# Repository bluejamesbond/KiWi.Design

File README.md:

Bolt.Design
===========

**Colors:**
*pink*: `#c13eca`
*purple*: `#50248b`
*dark blue*: `#171d25`

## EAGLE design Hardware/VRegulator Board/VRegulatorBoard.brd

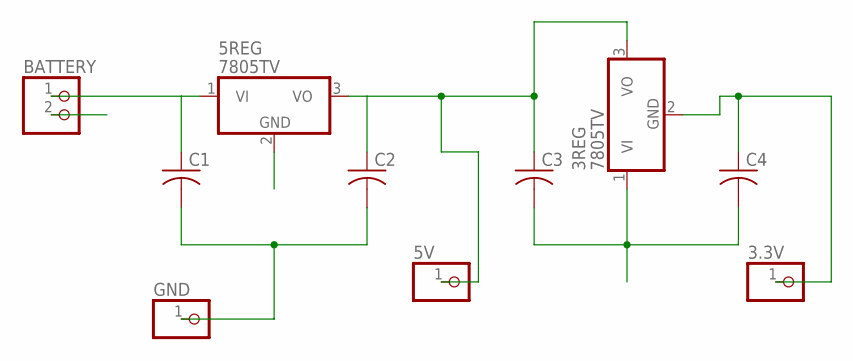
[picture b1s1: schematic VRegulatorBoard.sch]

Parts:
3.3V, 5V: PINHD-1X1; 1X01
3REG, 5REG: 7805TV; TO220V
BATTERY: PINHD-1X2; 1X02
C1, C2, C3, C4: C-US050-025X075; C050-025X075
GND: PINHD-1X1; 1X01

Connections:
5REGULATOR: 5REG.1 (VI), BATTERY.1, C1.1
GND: 3REG.1 (VI), 5REG.2 (GND), BATTERY.2, C1.2, C2.2, C3.2, C4.2, GND.1
unnamed: 3REG.3 (VO), 5REG.3 (VO), 5V.1, C2.1, C3.1
unnamed: 3.3V.1, 3REG.2 (GND), C4.1

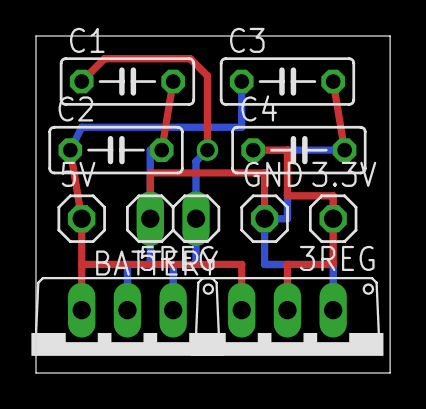
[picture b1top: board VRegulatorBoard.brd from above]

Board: 2 copper layers, 19.7 x 18.7 mm, 10 parts (0 on the bottom side), 4 nets.

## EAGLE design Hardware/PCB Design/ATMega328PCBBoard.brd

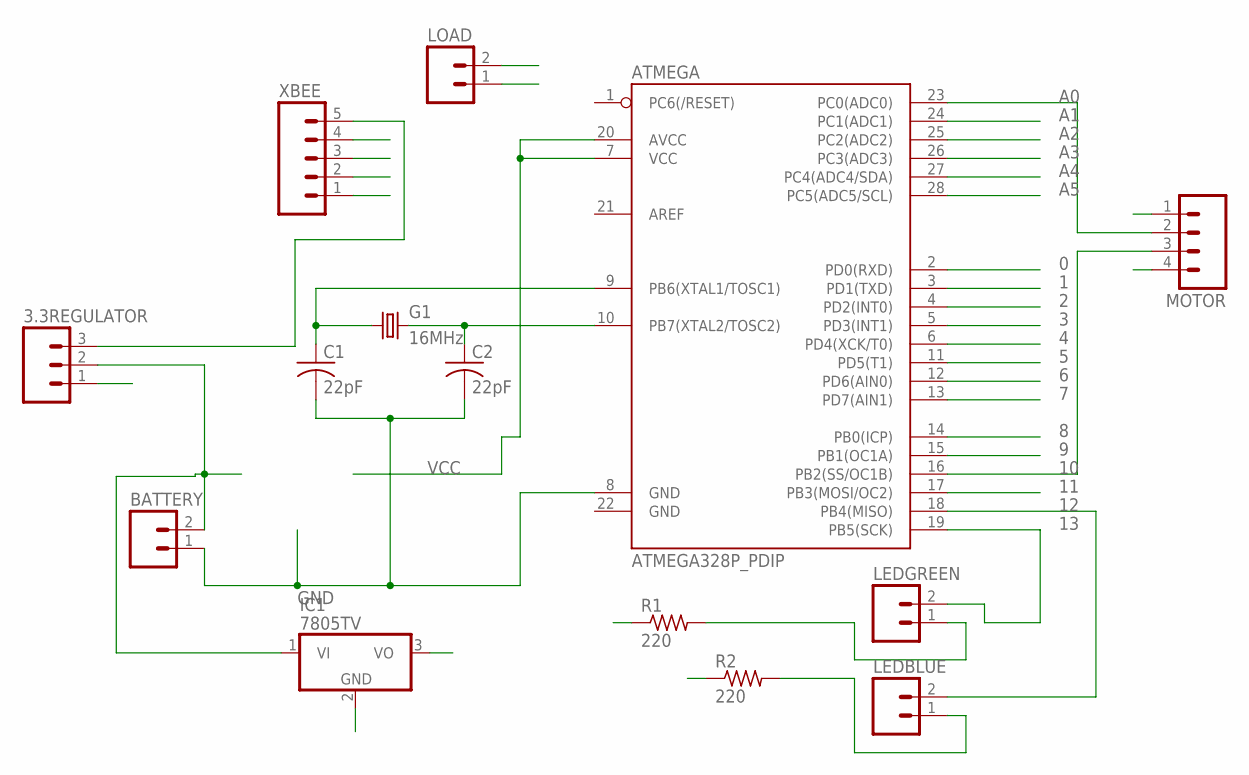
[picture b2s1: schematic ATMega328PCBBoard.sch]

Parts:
3.3REGULATOR: M03JST-PTH-VERT; JST-3-PTH-VERT
ATMEGA: ATMEGA328P_PDIP; DIL28-3
BATTERY: M02JST-PTH-VERT; JST-2-PTH-VERT
C1, C2: 22pF; C050-025X075
G1: 16MHz; HC49US
IC1: 7805TV; TO220V
LEDBLUE: M02JST-PTH-VERT; JST-2-PTH-VERT
LEDGREEN: M02JST-PTH-VERT; JST-2-PTH-VERT
LOAD: M02JST-PTH-VERT; JST-2-PTH-VERT
MOTOR: M04JST; 1X04-1.5MM_JST
R1, R2: 220; 0207/2V
XBEE: M05JST-VERT; JST-5-PTH-VERT

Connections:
0: ATMEGA.2 (PD0(RXD)), LOAD.1, XBEE.4
1: ATMEGA.3 (PD1(TXD)), LOAD.2, XBEE.3
2: ATMEGA.4 (PD2(INT0))
3: ATMEGA.5 (PD3(INT1))
3VCC: 3.3REGULATOR.3, XBEE.5
4: ATMEGA.6 (PD4(XCK/T0))
5: ATMEGA.11 (PD5(T1))
6: ATMEGA.12 (PD6(AIN0))
7: ATMEGA.13 (PD7(AIN1)), XBEE.1
8: ATMEGA.14 (PB0(ICP))
9: ATMEGA.15 (PB1(OC1A))
10: ATMEGA.16 (PB2(SS/OC1B)), MOTOR.3
11: ATMEGA.17 (PB3(MOSI/OC2))
12: ATMEGA.18 (PB4(MISO)), LEDBLUE.2
13: ATMEGA.19 (PB5(SCK)), LEDGREEN.2
A0: ATMEGA.23 (PC0(ADC0)), MOTOR.2
A1: ATMEGA.24 (PC1(ADC1))
A2: ATMEGA.25 (PC2(ADC2))
A3: ATMEGA.26 (PC3(ADC3))
A4: ATMEGA.27 (PC4(ADC4/SDA))
A5: ATMEGA.28 (PC5(ADC5/SCL))
GND: 3.3REGULATOR.1, ATMEGA.8 (GND), BATTERY.1, C1.2, C2.2, IC1.2 (GND), MOTOR.4, R1.1, R2.1, XBEE.2
unnamed: ATMEGA.10 (PB7(XTAL2/TOSC2)), C2.1, G1.2
unnamed: ATMEGA.9 (PB6(XTAL1/TOSC1)), C1.1, G1.1
unnamed: LEDGREEN.1, R1.2
unnamed: 3.3REGULATOR.2, BATTERY.2, IC1.1 (VI)
unnamed: LEDBLUE.1, R2.2
VCC: ATMEGA.7 (VCC), ATMEGA.20 (AVCC), IC1.3 (VO), MOTOR.1

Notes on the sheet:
GND
VCC

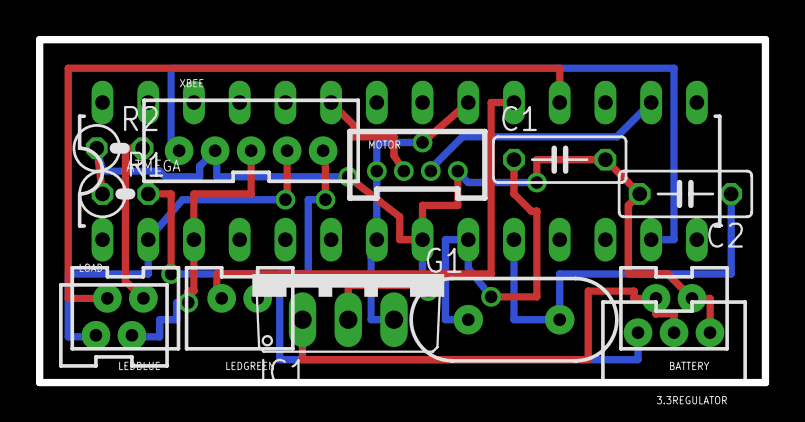
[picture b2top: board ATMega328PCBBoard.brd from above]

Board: 2 copper layers, 40.3 x 19.1 mm, 14 parts (0 on the bottom side), 15 nets.

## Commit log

2014-10-31 Initial push
2014-12-01 Adding IOS design
2014-12-01 added opening screen
2014-12-01 added open-screen.png
2014-12-02 Adding photoshop files
2014-12-03 pusing opening-sceren
2015-01-14 Added colors + changed some things
2015-01-14 Added first iteration of my logo designs
2015-01-29 Bad designs
2015-03-04 added illustrator file
    please make a copy of it if you want to work on your own version
2015-03-23 logo changes
2015-03-24 Adding logos
2015-03-31 added my white space logo
2015-03-31 updated psd file
2015-04-15 Cleaned out directories + added pcb files
2015-04-15 updated pcb design, waiting on xbee circuit
2015-04-16 finished pcb
2015-04-16 small update
2015-04-19 updated pcb
2015-04-19 fixed board
2015-04-19 sol for pcb
2015-04-19 updated board
2015-04-20 updated board again
2015-04-20 final board design
2015-04-24 updated boards + logo 6 in illustrator
2015-04-25 added regulator board
2015-04-26 Adding packing
2015-04-26 added indesign file
2015-04-26 Adding logo
2015-05-06 Adding renders
2015-05-06 Updating images

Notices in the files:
parts and their libraries:
SparkFun-DigitalIC: Licensing: Creative Commons ShareAlike 4.0 International - https://creativecommons.org/licenses/by-sa/4.0
